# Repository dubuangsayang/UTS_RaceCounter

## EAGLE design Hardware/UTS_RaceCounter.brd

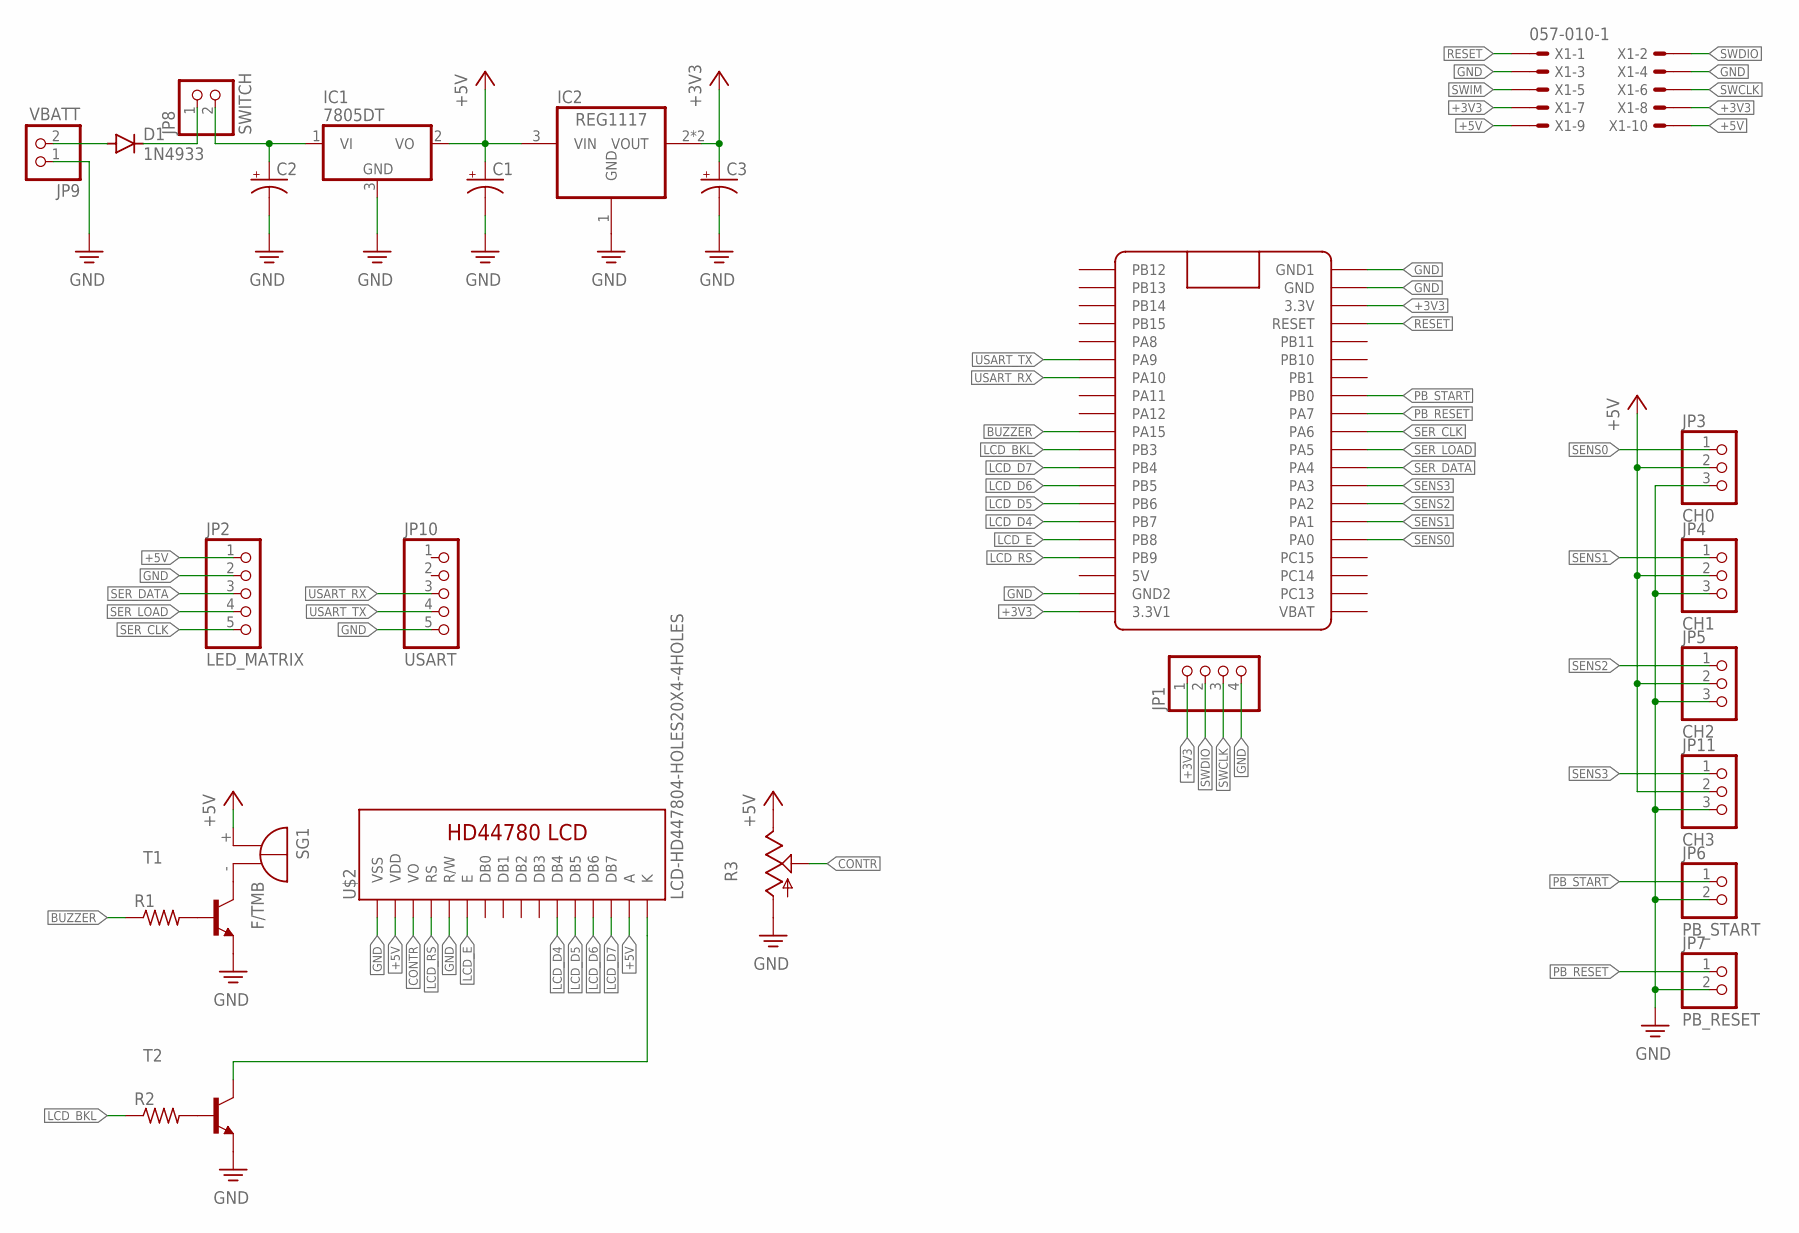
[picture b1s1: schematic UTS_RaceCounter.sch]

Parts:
C1, C2, C3: CPOL-USE2.5-6; E2,5-6
D1: 1N4933; DO41-10
IC1: 7805DT; TO252
IC2: REG1117; SOT223
JP1: PINHD-1X4; 1X04
JP2: LED_MATRIX; 1X05
JP3: CH0; 1X03
JP4: CH1; 1X03
JP5: CH2; 1X03
JP6: PB_START; 1X02
JP7: PB_RESET; 1X02
JP8: SWITCH; 1X02
JP9: VBATT; 1X02
JP10: USART; 1X05
JP11: CH3; 1X03
R1, R2: R-US_0204/7; 0204/7
R3: TRIM_US-CA6V; CA6V
SG1: F/TMB
T1, T2: BC167-NPN-TO92-ECB; TO92-ECB
U$1: BLUE_PILL
U$2: LCD-HD447804-HOLES20X4-4HOLES; LCD-20X4-4HOLES
X1: 057-010-1

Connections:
+3V3: C3.+, IC2.2 (VOUT), IC2.4 (VOUT), JP1.1, U$1.P$20 (3.3V1), U$1.P$23 (3.3V), X1.7, X1.8
+5V: C1.+, IC1.2 (VO), IC2.3 (VIN), JP2.1, JP3.2, JP4.2, JP5.2, JP11.2, R3.E, SG1.+, U$2.P$2 (VDD), U$2.P$15 (A), X1.9, X1.10
BUZZER: R1.1, U$1.P$10 (PA15)
CONTR: R3.S, U$2.P$3 (VO)
GND: C1.-, C2.-, C3.-, IC1.3 (GND), IC2.1 (GND), JP1.4, JP2.2, JP3.3, JP4.3, JP5.3, JP6.2, JP7.2, JP9.1, JP10.5, JP11.3, R3.A, T1.E, T2.E, U$1.P$19 (GND2), U$1.P$21 (GND1), U$1.P$22 (GND), U$2.P$1 (VSS), U$2.P$5 (R/W), X1.3, X1.4
LCD_BKL: R2.1, U$1.P$11 (PB3)
LCD_D4: U$1.P$15 (PB7), U$2.P$11 (DB4)
LCD_D5: U$1.P$14 (PB6), U$2.P$12 (DB5)
LCD_D6: U$1.P$13 (PB5), U$2.P$13 (DB6)
LCD_D7: U$1.P$12 (PB4), U$2.P$14 (DB7)
LCD_E: U$1.P$16 (PB8), U$2.P$6 (E)
LCD_RS: U$1.P$17 (PB9), U$2.P$4 (RS)
unnamed: SG1.-, T1.C
unnamed: R1.2, T1.B
unnamed: R2.2, T2.B
unnamed: C2.+, IC1.1 (VI), JP8.2
unnamed: D1.C, JP8.1
unnamed: D1.A, JP9.2
unnamed: T2.C, U$2.P$16 (K)
PB_RESET: JP7.1, U$1.P$29 (PA7)
PB_START: JP6.1, U$1.P$28 (PB0)
RESET: U$1.P$24 (RESET), X1.1
SENS0: JP3.1, U$1.P$36 (PA0)
SENS1: JP4.1, U$1.P$35 (PA1)
SENS2: JP5.1, U$1.P$34 (PA2)
SENS3: JP11.1, U$1.P$33 (PA3)
SER_CLK: JP2.5, U$1.P$30 (PA6)
SER_DATA: JP2.3, U$1.P$32 (PA4)
SER_LOAD: JP2.4, U$1.P$31 (PA5)
SWCLK: JP1.3, X1.6
SWDIO: JP1.2, X1.2
SWIM: X1.5
USART_RX: JP10.3, U$1.P$7 (PA10)
USART_TX: JP10.4, U$1.P$6 (PA9)

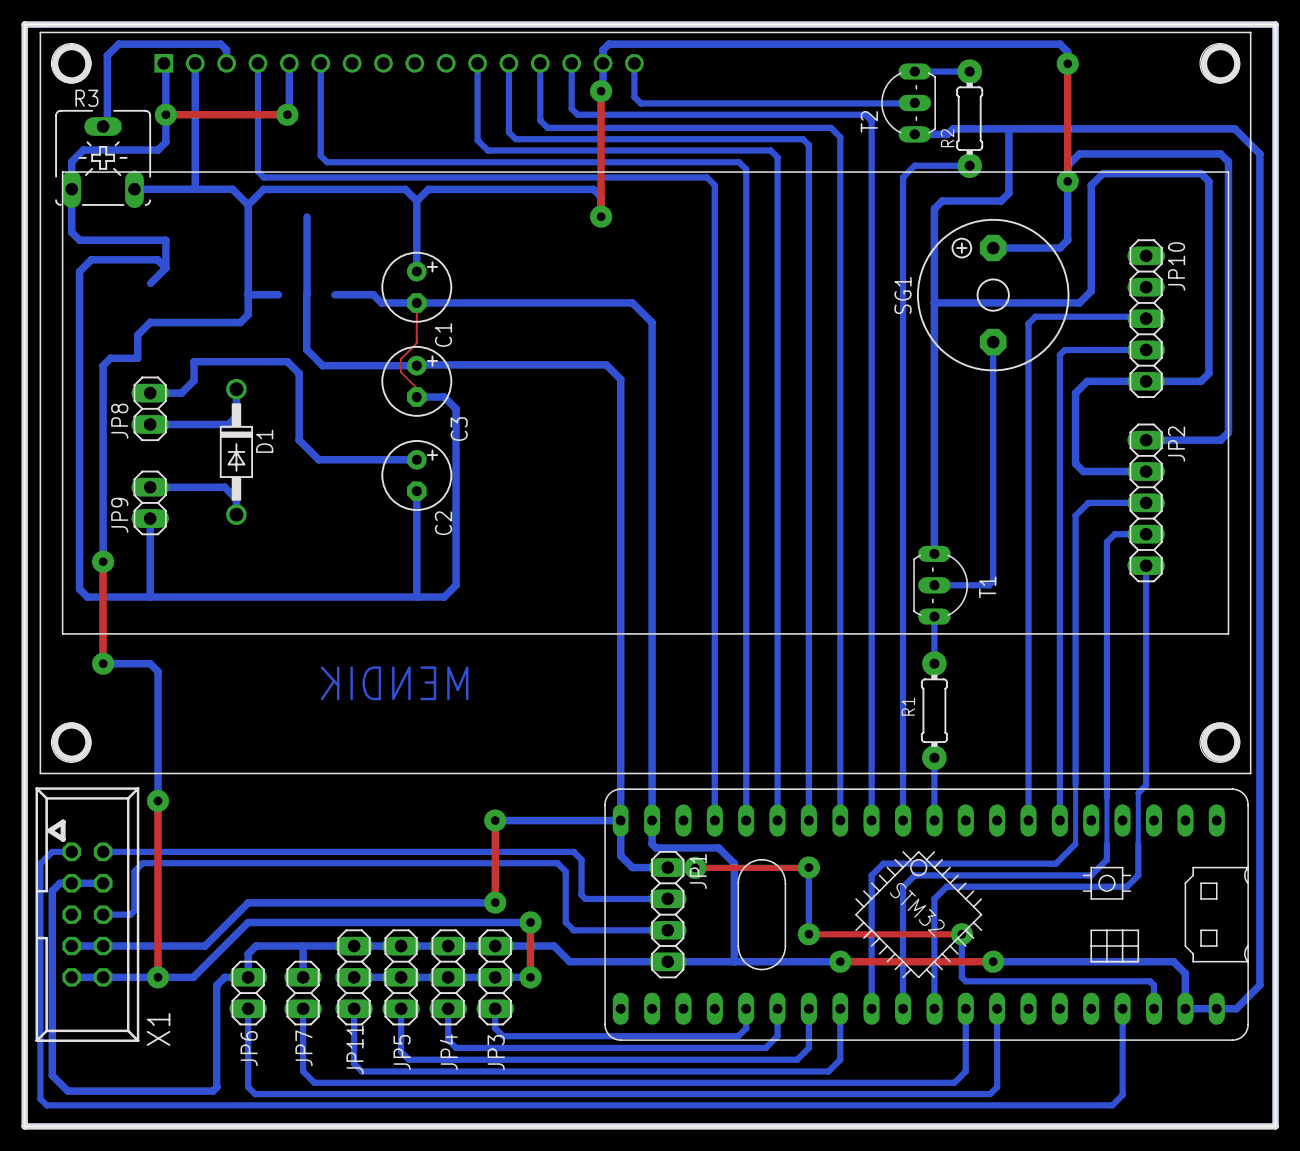
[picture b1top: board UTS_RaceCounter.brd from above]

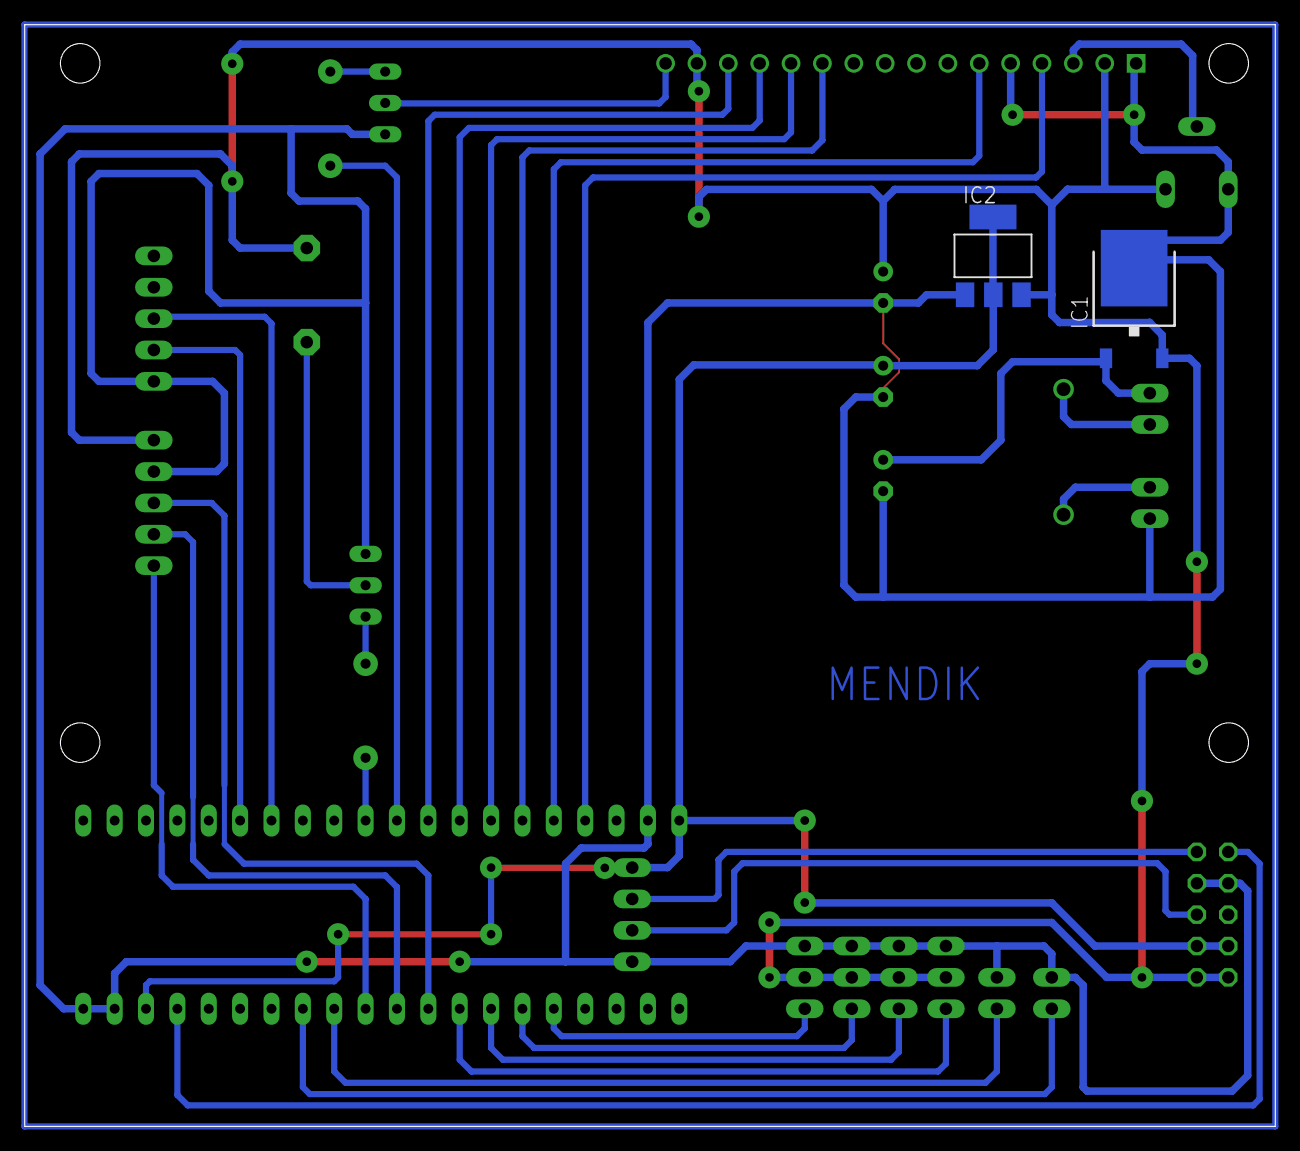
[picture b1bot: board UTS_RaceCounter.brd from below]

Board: 2 copper layers, 101.3 x 89.2 mm, 26 parts (2 on the bottom side), 33 nets.

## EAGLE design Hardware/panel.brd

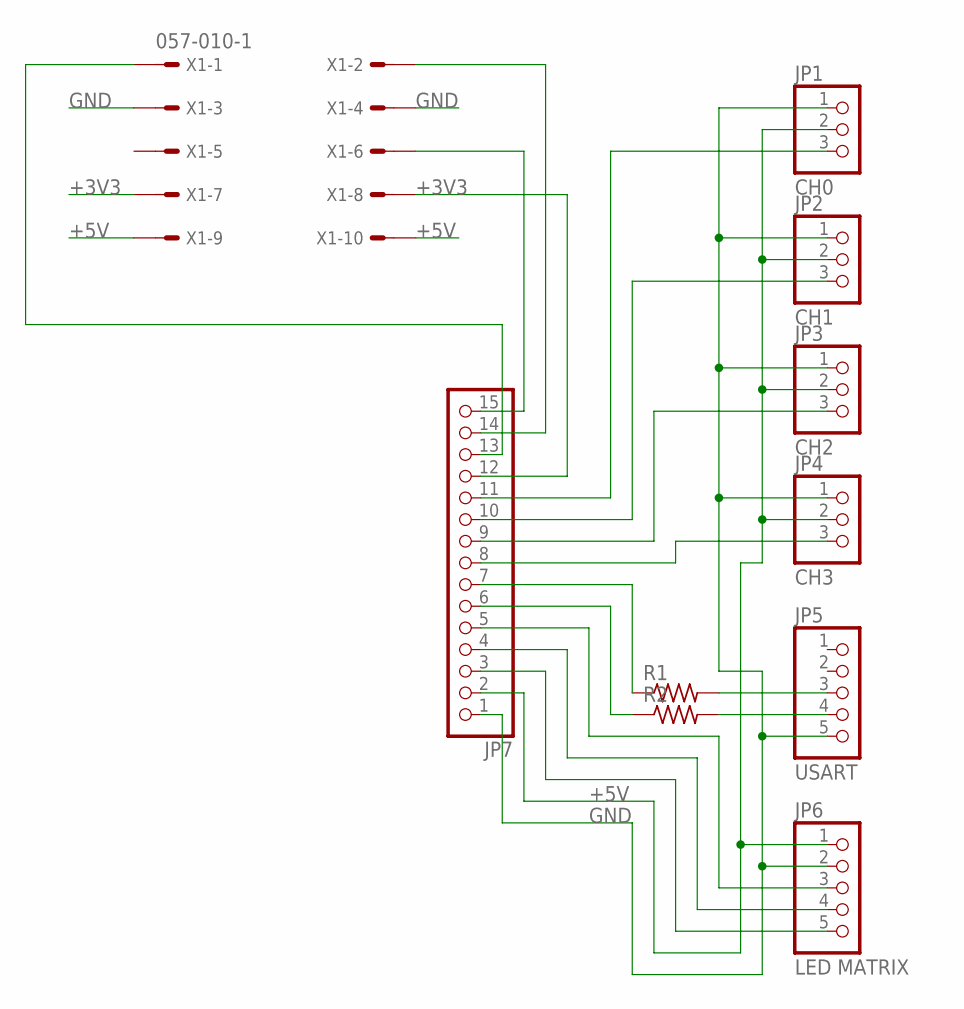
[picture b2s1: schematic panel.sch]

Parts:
JP1: CH0; 1X03
JP2: CH1; 1X03
JP3: CH2; 1X03
JP4: CH3; 1X03
JP5: USART; 1X05
JP6: LED MATRIX; 1X05
JP7: PINHD-1X15; 1X15
R1, R2: R-US_0204/7; 0204/7
X1: 057-010-1

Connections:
+3V3: JP7.12, X1.7, X1.8
+5V: JP1.2, JP2.2, JP3.2, JP4.2, JP6.1, JP7.2, X1.9, X1.10
GND: JP1.1, JP2.1, JP3.1, JP4.1, JP5.5, JP6.2, JP7.1, X1.3, X1.4
unnamed: JP5.3, R1.2
unnamed: JP7.6, R2.1
unnamed: JP5.4, R2.2
unnamed: JP1.3, JP7.11
unnamed: JP2.3, JP7.10
unnamed: JP4.3, JP7.8
unnamed: JP3.3, JP7.9
unnamed: JP7.7, R1.1
unnamed: JP6.3, JP7.5
unnamed: JP6.4, JP7.4
unnamed: JP6.5, JP7.3
unnamed: JP7.13, X1.1
unnamed: JP7.14, X1.2
unnamed: JP7.15, X1.6

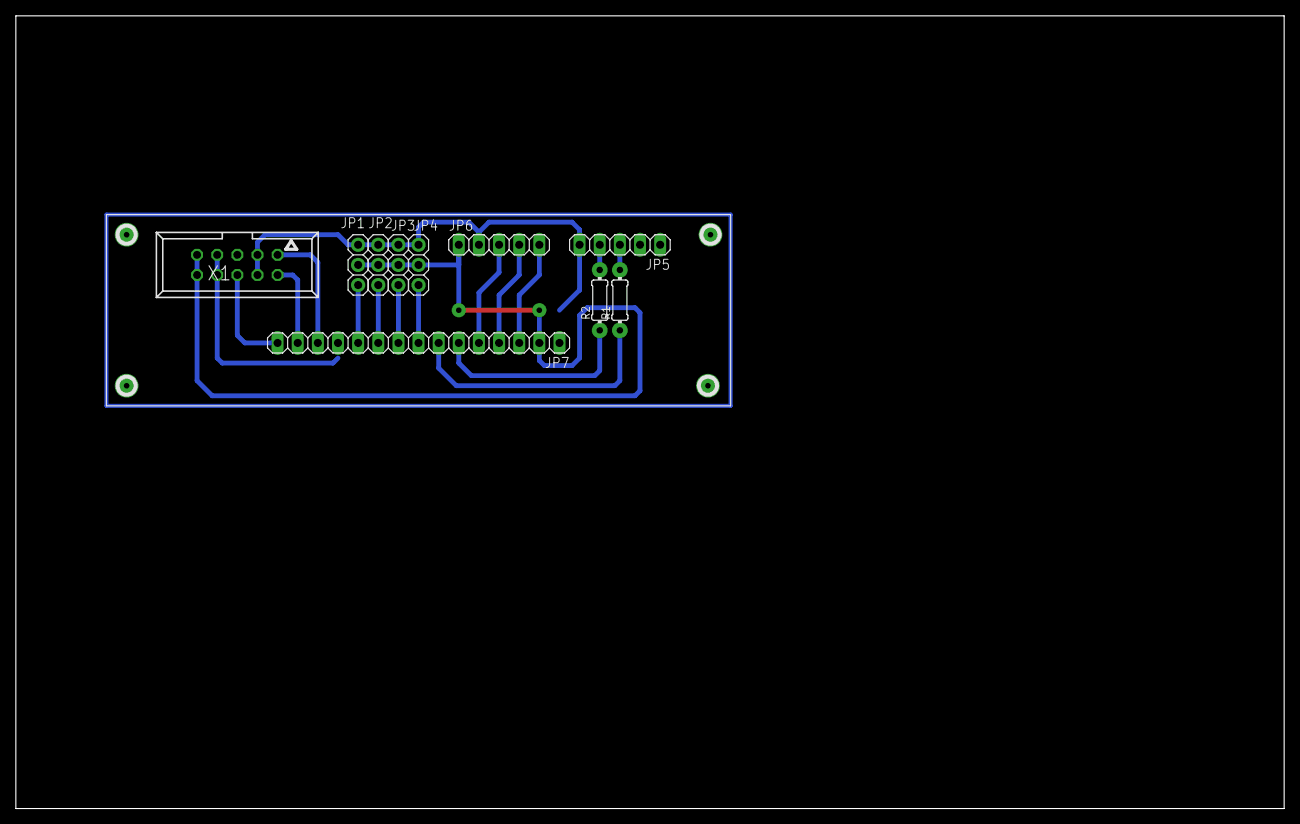
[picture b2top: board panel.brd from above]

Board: 2 copper layers, 160.0 x 100.0 mm, 10 parts (0 on the bottom side), 17 nets.

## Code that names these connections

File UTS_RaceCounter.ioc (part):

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Mcu.Name=STM32F103C(8-B)Tx
Mcu.Package=LQFP48
Mcu.UserName=STM32F103C8Tx
PA0-WKUP.Signal=ADCx_IN0
PA1.Signal=ADCx_IN1
PA10.Mode=Asynchronous
PA10.Signal=USART1_RX
PA13.Mode=Serial_Wire
PA13.Signal=SYS_JTMS-SWDIO
PA14.Mode=Serial_Wire
PA14.Signal=SYS_JTCK-SWCLK
PA15.GPIOParameters=GPIO_Label
PA15.GPIO_Label=Buzzer
PA15.Signal=GPIO_Output
PA2.Signal=ADCx_IN2
PA3.Signal=ADCx_IN3
PA4.GPIOParameters=GPIO_Label
PA4.GPIO_Label=Ser_Data
PA4.Signal=GPIO_Output
PA5.GPIOParameters=GPIO_Label
PA5.GPIO_Label=Ser_Load
PA5.Signal=GPIO_Output
PA6.GPIOParameters=GPIO_Label
PA6.GPIO_Label=Ser_Clk
PA6.Signal=GPIO_Output
PA7.GPIOParameters=GPIO_PuPd,GPIO_Label
PA7.GPIO_Label=PB_RESET
PA7.GPIO_PuPd=GPIO_PULLUP
PA7.Signal=GPIO_Input
PA9.Mode=Asynchronous
PA9.Signal=USART1_TX
PB0.GPIOParameters=GPIO_PuPd,GPIO_Label
PB0.GPIO_Label=PB_START
PB0.GPIO_PuPd=GPIO_PULLUP
PB0.Signal=GPIO_Input
PB3.GPIOParameters=GPIO_Label
PB3.GPIO_Label=LCD_Bkl
PB3.Signal=GPIO_Output
PB4.GPIOParameters=GPIO_Label
PB4.GPIO_Label=LCD_D7
PB4.Signal=GPIO_Output
PB5.GPIOParameters=GPIO_Label
PB5.GPIO_Label=LCD_D6
PB5.Signal=GPIO_Output
PB6.GPIOParameters=GPIO_Label
PB6.GPIO_Label=LCD_D5
PB6.Signal=GPIO_Output
PB7.GPIOParameters=GPIO_Label
PB7.GPIO_Label=LCD_D4
PB7.Signal=GPIO_Output
PB8.GPIOParameters=GPIO_Label
PB8.GPIO_Label=LCD_E
PB8.Signal=GPIO_Output
PB9.GPIOParameters=GPIO_Label
PB9.GPIO_Label=LCD_RS
PB9.Signal=GPIO_Output
PD0-OSC_IN.Mode=HSE-External-Oscillator
PD0-OSC_IN.Signal=RCC_OSC_IN
PD1-OSC_OUT.Mode=HSE-External-Oscillator
PD1-OSC_OUT.Signal=RCC_OSC_OUT
RCC.SYSCLKFreq_VALUE=72000000
RCC.SYSCLKSource=RCC_SYSCLKSOURCE_PLLCLK
board=custom

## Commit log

2019-11-01 second commit
2019-11-01 third commit
2019-11-01 menambahakan file dalam gitignore
2019-11-01 fouth commit
2019-11-02 Adding timeout feature & resetting using button
2019-11-02 ADC stucked2
2019-11-02 Adding timer capture1
2019-11-02 Adding timer capture2
2019-11-03 memperbaiki master
2019-11-03 memperbaiki advanced2
2019-11-03 mau branch baru
2019-11-03 Penambahan Display LED Matrix
2019-11-03 Penambahan UART
2019-11-03 File terstruktur
2019-11-03 Penambaahan UART
2019-11-03 Program bug
2019-11-03 Program Buzzer On
2019-11-03 Program Bug1
2019-11-03 Penambahan fitur kalibrasi
2019-11-03 hapus komen yang tidak perlu
2019-11-04 Sudah demo
2019-11-04 Penambahan dokumen dan skematik
